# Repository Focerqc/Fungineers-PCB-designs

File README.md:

# Fungineers PCB designs

Boards for Fungineers hardware: the 32s pack BMS, the Superflux hall board, Funwheel light bars, and the connectors that sit in the controller box.

A reference photo, an OEM drawing, or a chip vendor's eval board tells us the job and the shape. The board in this repo is finished when it does that job with the parts that are already on it. A different FET, a module instead of a bare chip, or a bleed resistor the eval board never had is fine when the circuit still measures, drives, or lights what it has to. A silk screen that matches a photo, with nets that do not complete the job, is not finished.

## Boards

| Folder | Status | Job |
|---|---|---|
| [`qfbms32 ai pcb/`](qfbms32%20ai%20pcb/README.md) | Incomplete | 32s BMS. Dual BQ76952, ESP32-C3, pack and charge connectors, cell taps, thermistors, CAN. Parts are placed. The circuit is not finished. |
| [`sf hall ai pcb/`](sf%20hall%20ai%20pcb/README.md) | Laid out | Hall board for the Superflux stator. Three sensors on the stator pitch, purple mask, ENIG. |
| [`Funwheel LED strips/`](Funwheel%20LED%20strips/README.md) | Laid out | Funwheel X7 headlight, taillight, and Thor300 status bars. Each size has its own readme. |
| [`footpad connector controller box side/`](footpad%20connector%20controller%20box%20side/README.md) | Laid out | Small breakouts for the controller enclosure: 5-pin Amphenol and 6-pin Switchcraft / Molex. |
| [`GTFO/`](GTFO/README.md) | Photos only | Reference photos for the GTFO lights and the GTS-FO BMS adapter. The laid-out LED boards are under `Funwheel LED strips/`. |
| [`FM VFBMS adapter/`](FM%20VFBMS%20adapter/README.md) | Stopped | Adapter between a Fungineers BMS and the GTFO controller. No board was made. |
| `_reference/firmware/` | Notes | Notes for the smaller charge-only VBMS32, not the 32s board. |
| `_tools/` | Local tools | Board boxes on port 5180. BMS progress, read from the PCB file, on port 5181. |

## KiCad

Boards are KiCad 10 projects. Open the `.kicad_pro` in the folder you mean to work on. Scripts that import `pcbnew` have to run with `C:\Program Files\KiCad\10.0\bin\python.exe`.

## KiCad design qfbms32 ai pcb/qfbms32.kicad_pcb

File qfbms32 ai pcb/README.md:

# qfbms32

32-series BMS for a Fungineers pack. The board is a long strip, about 130 × 32 mm, two layers.

The parts are already placed to match the photos in `_reference/user_photos/`. Those positions, rotations, and packages stay. The work left is electrical: the placed parts have to do the BMS job.

## The job

The pack harness is `_reference/vfbms32_wiring_32s_best.jpg`. That drawing says which wire lands where. It is not a schematic.

| What the pack needs | On this board |
|---|---|
| Pack positive and negative | `J_BAT1` — TOP CELL is `CELL32`, BOT is `CELL0` |
| Charger | `J_CHG1` — `CHG+` / `CHG−` |
| 32 series cells, 33 taps | `J_CELL4` … `J_CELL1`, left to right `CELL32` … `CELL0` |
| Four thermistors | `J_T1` … `J_T4` |
| ESC CAN and 5 V | `J_COMM1`, through the isolator `U7` |
| Enable, buzzer, USB | Have to exist as a circuit, not only as a picture on the harness sheet |

Behind those connectors the board has to:

- Measure every cell on two BQ7695202s. `U_BQ1` is the low 16 (`CELL0`…`CELL16`). `U_BQ2` is the high 16 (`CELL16`…`CELL32`).
- Measure pack current on the shunt (`R_SH1`, `R_SH2`) through `SRP` / `SRN`.
- Bias and read the thermistors.
- Let the ESP32-C3 (`U_ESP1`) talk to both monitors.
- Switch charge (`Q1`) and discharge (`Q2`). `U_SSR1` is the gate helper that is actually placed. The BQ charge and discharge pins can drive gates too, once they are wired.
- Power the logic. `U4` is the buck that is placed for that.

The TI BQ76952 datasheet and EVM (under `_reference/ti_bq76952/`) supply pin function and the usual values: 20 Ω and 0.22 µF on each cell input, regulator caps, a sense filter, 10 kΩ thermistor bias. Use those values on the parts that are already here. Do not move a part to make the eval-board layout fit.

The placed chip stays even when it is a different part than the reference. `U_ESP1` is an ESP32-C3-MINI-1. The FETs are AGM15T03LL. The relay is an H2440. `R_B1`–`R_B33` are the 27 Ω bleed row beside the cell connectors. If a placed part has no pin for a function the reference wanted, stop and say which ref and which pin.

## Where it stands

This folder is the only copy of the board. Scored from the PCB file, not from notes. Open the progress dashboard and hit Reload after the board changes:

```powershell
python _tools/progress_dashboard/server.py
# http://localhost:5181
```

As of 27 Oct 2026 the file says:

- Connector names for pack, charge, the 33 cell taps, the four temps, and CAN match the harness.
- All 32 cell taps share copper with their filter resistor (`R_F`, 20 Ω). None of those resistors reach a BQ pin. The 0.22 µF caps (`C_F`) are on the back with nets and no copper.
- `U_BQ1` has 24 of 48 pins named. `U_BQ2` has 22. No BQ pin has copper to another part. Regulator, I2C, and the BQ FET-driver pins are empty. `BAT` is shorted to the `VC16` net. `VC0` on `U_BQ1` is tied straight to `CELL0`.
- The fuse input shares copper with TOP CELL. The fuse does not reach the FET drains. The shunt does not reach `SRP` / `SRN`. Neither FET gate reaches a driver.
- `U_ESP1`, USB-C, and the buck have no nets. There is no enable switch. The buzzer has a net name and nothing driving it.
- `R_B1`–`R_B33` are placed and unnetted. Leave them where they are.

The PCB pad nets are the working copy. The schematic has labels for the same idea and is not ahead of the board.

## Files

| Path | What it is |
|---|---|
| `qfbms32.kicad_pro` | KiCad 10 project |
| `qfbms32.kicad_pcb` | Layout. This is the board. |
| `qfbms32.kicad_sch` | Schematic |
| `WORKING_TOPOLOGY.md` | Net names for the harness and the two monitors |
| `qfbms.pretty/` | Footprints that are not in KiCad stock |
| `_reference/vfbms32_wiring_32s_best.jpg` | Pack harness drawing |
| `_reference/user_photos/` | The placed board, which the footprints have to match |
| `_reference/ti_bq76952/` | Datasheet, EVM guide, TIDA-010208 |
| `.history/` | Copies taken before large edits |
| `scratch/` | One-off scripts and the AGM pinout notes. Not part of the design. |

## Editing

Do not move, rotate, or swap a footprint to copy TI, to open a routing channel, or because the part looks unused. Route around it. Ask before a position, a footprint, or a value changes. The same rule is in `.cursor/rules/qfbms32-placement.mdc`.

KiCad's Python, for anything that imports `pcbnew`:

```powershell
& "C:\Program Files\KiCad\10.0\bin\python.exe" script.py
```

The other local tool, board boxes, is the placement viewer on port 5180 (`python _tools/pcb_dashboard/server.py`). It does not score whether the circuit works.

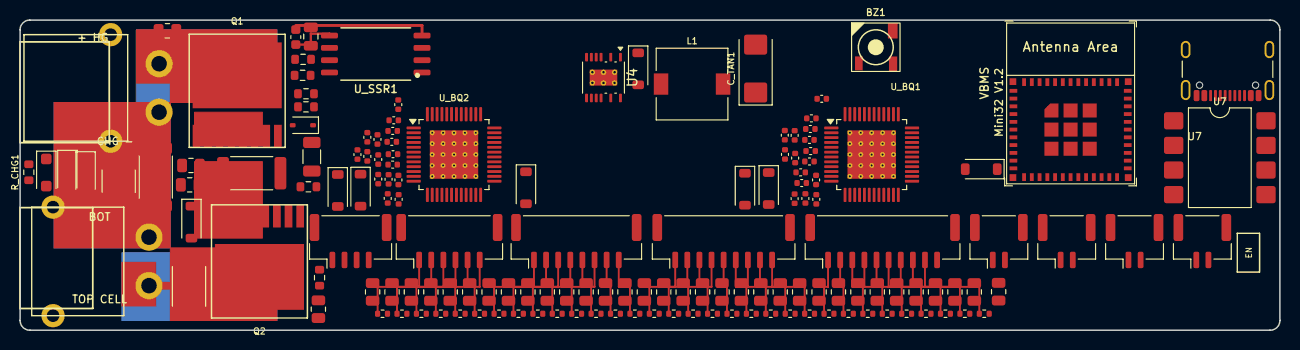
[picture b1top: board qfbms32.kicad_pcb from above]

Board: 2 copper layers, 130.0 x 32.0 mm, 150 parts (0 on the bottom side), 85 nets.

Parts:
BZ1: FUET-5030; Buzzer_5.0x5.0mm_SMD
C_DISC: 10uF; C_1206_3216Metric
C_F1, C_F2, C_F3, C_F4, C_F5, C_F6, C_F7, C_F8, C_F9, C_F10, C_F11, C_F12, C_F13, C_F14, C_F15, C_F16, C_F17, C_F18, C_F19, C_F20, C_F21, C_F22, C_F23, C_F24, C_F25, C_F26, C_F27, C_F28, C_F29, C_F30, C_F31, C_F32: 0.22uF; C_0402_1005Metric
C_FLT1: 10uF_100V; C_1812_4532Metric
C_SSR1: 100nF; C_0603_1608Metric
C_SSR2: 1uF; C_0805_2012Metric
C_TAN1: 100uF_16V; CP_EIA-6032-28_Kemet-C
D_BST1: Schottky; D_SOD-123
D_CHG1, D_CHG2, D_CHG3: DSK320; D_SOD-123F
D_GS1: PDZ16B; D_SOD-323
D_PRI1, D_PRI2, D_PRI3: D_Schottky; D_SOD-123
D_S1: TVS; D_SOD-123
D_SEC1, D_SEC2, D_SEC3: D_Schottky; D_SOD-123
F1: JT 15A; Fuse_2512_6332Metric
FB1: Unmarked; R_0603_1608Metric
J_BAT1: XT30PW-M (BAT); XT30PW-M_Lugs
J_CELL1: 0-8; JST_GH_BM10B-GHS-TBT_1x10-1MP_P1.25mm_Vertical
J_CELL2: 9-16; JST_GH_BM09B-GHS-TBT_1x09-1MP_P1.25mm_Vertical
J_CELL3: 17-24; JST_GH_BM08B-GHS-TBT_1x08-1MP_P1.25mm_Vertical
J_CELL4: 25-32; JST_GH_BM06B-GHS-TBT_1x06-1MP_P1.25mm_Vertical
J_CHG1: XT30PW-F (CHG); XT30PW-F_Lugs
J_COMM1: CAN/5V; JST_GH_BM04B-GHS-TBT_1x04-1MP_P1.25mm_Vertical
J_T1: T1; JST_GH_BM02B-GHS-TBT_1x02-1MP_P1.25mm_Vertical
J_T2: T2; JST_GH_BM02B-GHS-TBT_1x02-1MP_P1.25mm_Vertical
J_T3: T3; JST_GH_BM02B-GHS-TBT_1x02-1MP_P1.25mm_Vertical
J_T4: T4; JST_GH_BM02B-GHS-TBT_1x02-1MP_P1.25mm_Vertical
J_USB1: USB-C; USB_C_Receptacle_16P
L1: 180uH_181; L_7.3x7.3_H4.5
Q1, Q2: AGM15T03LL; TOLL-8_AGM15T03LL
R_B1, R_B2, R_B3, R_B4, R_B5, R_B6, R_B7, R_B8, R_B9, R_B10, R_B11, R_B12, R_B13, R_B14, R_B15, R_B16, R_B17, R_B18, R_B19, R_B20, R_B21, R_B22, R_B23, R_B24, R_B25, R_B26, R_B27, R_B28, R_B29, R_B30, R_B31, R_B32, R_B33: 27R0; R_0805_2012Metric
R_CHG1: 100k; R_0603_1608Metric
R_CHG2: 2203; R_0805_2012Metric
R_DSG1: 1000; R_0805_2012Metric
R_F1, R_F2, R_F3, R_F4, R_F5, R_F6, R_F7, R_F8, R_F9, R_F10, R_F11, R_F12, R_F13, R_F14, R_F15, R_F16, R_F17, R_F18, R_F19, R_F20, R_F21, R_F22, R_F23, R_F24, R_F25, R_F26, R_F27, R_F28, R_F29, R_F30, R_F31, R_F32: 20R; R_0402_1005Metric
R_G1: 01X; R_0603_1608Metric
R_GS1: 474; R_0603_1608Metric
R_S1, R_S2: 1000; R_0805_2012Metric
R_SEC1: 01X; R_0603_1608Metric
R_SH1, R_SH2: R001; R_2512_6332Metric
R_SSR1: 01X; R_0603_1608Metric
R_SSR2: 10k; R_0603_1608Metric
U4: LTC7138; Analog_MSOP-12-16-1EP_3x4.039mm_P0.5mm_EP1.651x2.845mm_Ther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
U7: ISO1050 (DUB-8); SMDIP-8_W9.53mm
U_BQ1: BQ7695202 (IC1); TQFP-48-1EP_7x7mm_P0.5mm_EP5x5mm_ThermalVias
U_BQ2: BQ7695202 (IC2); TQFP-48-1EP_7x7mm_P0.5mm_EP5x5mm_ThermalVias
U_ESP1: ESP32-C3-MINI-1
U_SSR1: GSRELAY; H2440_SSR

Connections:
5VExt: J_COMM1.4, U7.8
+3V3: BZ1.1, U7.1
BQ1_VC1: C_F1.1, C_F2.2, R_F32.2, U_BQ1.15
BQ1_VC2: C_F2.1, C_F3.2, R_F31.2, U_BQ1.14
BQ1_VC3: C_F3.1, C_F4.2, R_F30.2, U_BQ1.13
BQ1_VC4: C_F4.1, C_F5.2, R_F29.2, U_BQ1.12
BQ1_VC5: C_F5.1, C_F6.2, R_F28.2, U_BQ1.11
BQ1_VC6: C_F6.1, C_F7.2, R_F27.2, U_BQ1.10
BQ1_VC7: C_F7.1, C_F8.2, R_F26.2, U_BQ1.9
BQ1_VC8: C_F8.1, C_F9.2, R_F25.2, U_BQ1.8
BQ1_VC9: C_F9.1, C_F10.2, R_F24.2, U_BQ1.7
BQ1_VC10: C_F10.1, C_F11.2, R_F23.2, U_BQ1.6
BQ1_VC11: C_F11.1, C_F12.2, R_F22.2, U_BQ1.5
BQ1_VC12: C_F12.1, C_F13.2, R_F21.2, U_BQ1.4
BQ1_VC13: C_F13.1, C_F14.2, R_F20.2, U_BQ1.3
BQ1_VC14: C_F14.1, C_F15.2, R_F19.2, U_BQ1.2
BQ1_VC15: C_F15.1, C_F16.2, R_F18.2, U_BQ1.1
BQ1_VC16: C_F16.1, R_F17.2, U_BQ1.48
BQ2_VC1: C_F17.1, C_F18.2, R_F16.2, U_BQ2.15
BQ2_VC2: C_F18.1, C_F19.2, R_F15.2, U_BQ2.14
BQ2_VC3: C_F19.1, C_F20.2, R_F14.2, U_BQ2.13
BQ2_VC4: C_F20.1, C_F21.2, R_F13.2, U_BQ2.12
BQ2_VC5: C_F21.1, C_F22.2, R_F12.2, U_BQ2.11
BQ2_VC6: C_F22.1, C_F23.2, R_F11.2, U_BQ2.10
BQ2_VC7: C_F23.1, C_F24.2, R_F10.2, U_BQ2.9
BQ2_VC8: C_F24.1, C_F25.2, R_F9.2, U_BQ2.8
BQ2_VC9: C_F25.1, C_F26.2, R_F8.2, U_BQ2.7
BQ2_VC10: C_F26.1, C_F27.2, R_F7.2, U_BQ2.6
BQ2_VC11: C_F27.1, C_F28.2, R_F6.2, U_BQ2.5
BQ2_VC12: C_F28.1, C_F29.2, R_F5.2, U_BQ2.4
BQ2_VC13: C_F29.1, C_F30.2, R_F4.2, U_BQ2.3
BQ2_VC14: C_F30.1, C_F31.2, R_F3.2, U_BQ2.2
BQ2_VC15: C_F31.1, C_F32.2, R_F2.2, U_BQ2.1
BQ2_VC16: C_F32.1, R_F1.2, U_BQ2.48
CANH: J_COMM1.1, U7.7
CANL: J_COMM1.2, U7.6
CELL0: C_F1.2, J_BAT1.2, J_CELL1.10, R_SH1.1, U_BQ1.16
CELL1: J_CELL1.9, R_F32.1
CELL2: J_CELL1.8, R_F31.1
CELL3: J_CELL1.7, R_F30.1
CELL4: J_CELL1.6, R_F29.1
CELL5: J_CELL1.5, R_F28.1
CELL6: J_CELL1.4, R_F27.1
CELL7: J_CELL1.3, R_F26.1
CELL8: J_CELL1.2, R_F25.1
CELL9: J_CELL1.1, R_F24.1
CELL10: J_CELL2.9, R_F23.1
CELL11: J_CELL2.8, R_F22.1
CELL12: J_CELL2.7, R_F21.1
CELL13: J_CELL2.6, R_F20.1
CELL14: J_CELL2.5, R_F19.1
CELL15: J_CELL2.4, R_F18.1
CELL16: C_F17.2, J_CELL2.3, R_F17.1, U_BQ2.16
CELL17: J_CELL2.2, R_F16.1
CELL18: J_CELL2.1, R_F15.1
CELL19: J_CELL3.8, R_F14.1
CELL20: J_CELL3.7, R_F13.1
CELL21: J_CELL3.6, R_F12.1
CELL22: J_CELL3.5, R_F11.1
CELL23: J_CELL3.4, R_F10.1
CELL24: J_CELL3.3, R_F9.1
CELL25: J_CELL3.2, R_F8.1
CELL26: J_CELL3.1, R_F7.1
CELL27: J_CELL4.6, R_F6.1
CELL28: J_CELL4.5, R_F5.1
CELL29: J_CELL4.4, R_F4.1
CELL30: J_CELL4.3, R_F3.1
CELL31: J_CELL4.2, R_F2.1
CELL32: F1.1, J_BAT1.1, J_CELL4.1, R_F1.1, U_SSR1.6
CELL32_FUSED: F1.2, Q1.D, Q2.D
CHG+: D_GS1.2, J_CHG1.1, Q1.2, Q1.3, Q1.4, Q1.5, Q1.6, Q1.7, Q1.8, R_GS1.2
CHG-: J_CHG1.2, R_SH2.2
GND: C_SSR1.2, C_SSR2.2, J_T1.2, J_T2.2, J_T3.2, J_T4.2, R_SSR2.2, U7.4, U_BQ1.17, U_BQ2.17, U_SSR1.4
ISO_GND: J_COMM1.3, U7.5
PACK+: Q2.2, Q2.3, Q2.4, Q2.5, Q2.6, Q2.7, Q2.8
Q1_GATE: D_GS1.1, Q1.1, R_G1.1, R_GS1.1, R_SSR1.2, R_SSR2.1
SHUNT_MID: R_SH1.2, R_SH2.1
SRN: U_BQ1.20, U_BQ2.20
SRP: U_BQ1.18, U_BQ2.18
SSR_OUT_CHG: R_G1.2, R_SSR1.1
TS1: J_T1.1, U_BQ1.21
TS2: J_T2.1, U_BQ1.22
TS3: J_T3.1, U_BQ1.23
TS4: J_T4.1, U_BQ2.21
VBOOST: C_SSR1.1, C_SSR2.1, U_SSR1.5

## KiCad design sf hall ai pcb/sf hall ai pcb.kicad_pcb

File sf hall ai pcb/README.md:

# Superflux Hall Sensor PCB

**Status:** Laid out. Three sensors sit on the stator pitch. The STEP export still does not model plated walls inside the hall slots.

High-precision hall sensor PCB designed for the Fungineers Superflux motor.

---

## 1. Design Overview

- **Layer Stackup**: 2-Layer FR4, 1.6 mm thickness
- **Solder Mask**: Purple (`#43135C` / `#591271`), matching Superflux motor branding
- **Surface Finish**: ENIG (Electroless Nickel Immersion Gold)
- **Stator Alignment**: Derived from original stator drawing `sf hall locations.DXF` (27-slot stator, $13.\overline{3}^\circ$ pitch)

### Hall Sensor Centers (at $R = 56.15\,\text{mm}$):
- **U1**: $23^\circ 20'$ ($23.3333^\circ$)
- **U2**: $63^\circ 20'$ ($63.3333^\circ$)
- **U3**: $103^\circ 20'$ ($103.3333^\circ$)
- **Sensor Pitch**: Exactly $40.000^\circ$ (3 stator teeth) between sensors.
- **Pin Spread**: $\pm 2.45^\circ$ ($2.40\,\text{mm}$ pitch) between outer pins and centered middle pin.

---

## 2. TODO / Future Work: Hall Slot 3D Edge Plating

> [!WARNING]
> **CAD Modeling Note — Hall Slot Edge Plating**
>
> The hall sensor slots currently have:
> - $1.25\,\text{mm}$ wide clean U-slots on `Edge.Cuts` with semicircular rounded bottoms ($R = 0.625\,\text{mm}$).
> - U-shaped copper solder lands on `F.Cu` and `B.Cu` framing each slot with zero protrusion into the slot or past the outer board edge.
>
> **Known CAD Limitation**:
> In physical manufacturing (e.g., JLCPCB castellated holes / edge plating), the internal vertical walls of these slots are plated with copper and immersion gold. However, the standard KiCad STEP export pipeline (`kicad-cli pcb export step`) does not generate 3D vertical copper plating along internal `Edge.Cuts` slot profiles—it only exports planar surface copper pads and cylindrical through-hole barrels.
>
> **Action Required**:
> The pads are close and functional for component clearance and leg passage, but need work later to accurately model the vertical edge plating in the CAD/STEP assembly (either via custom 3D STEP body injection or an updated KiCad castellated modeling workflow).

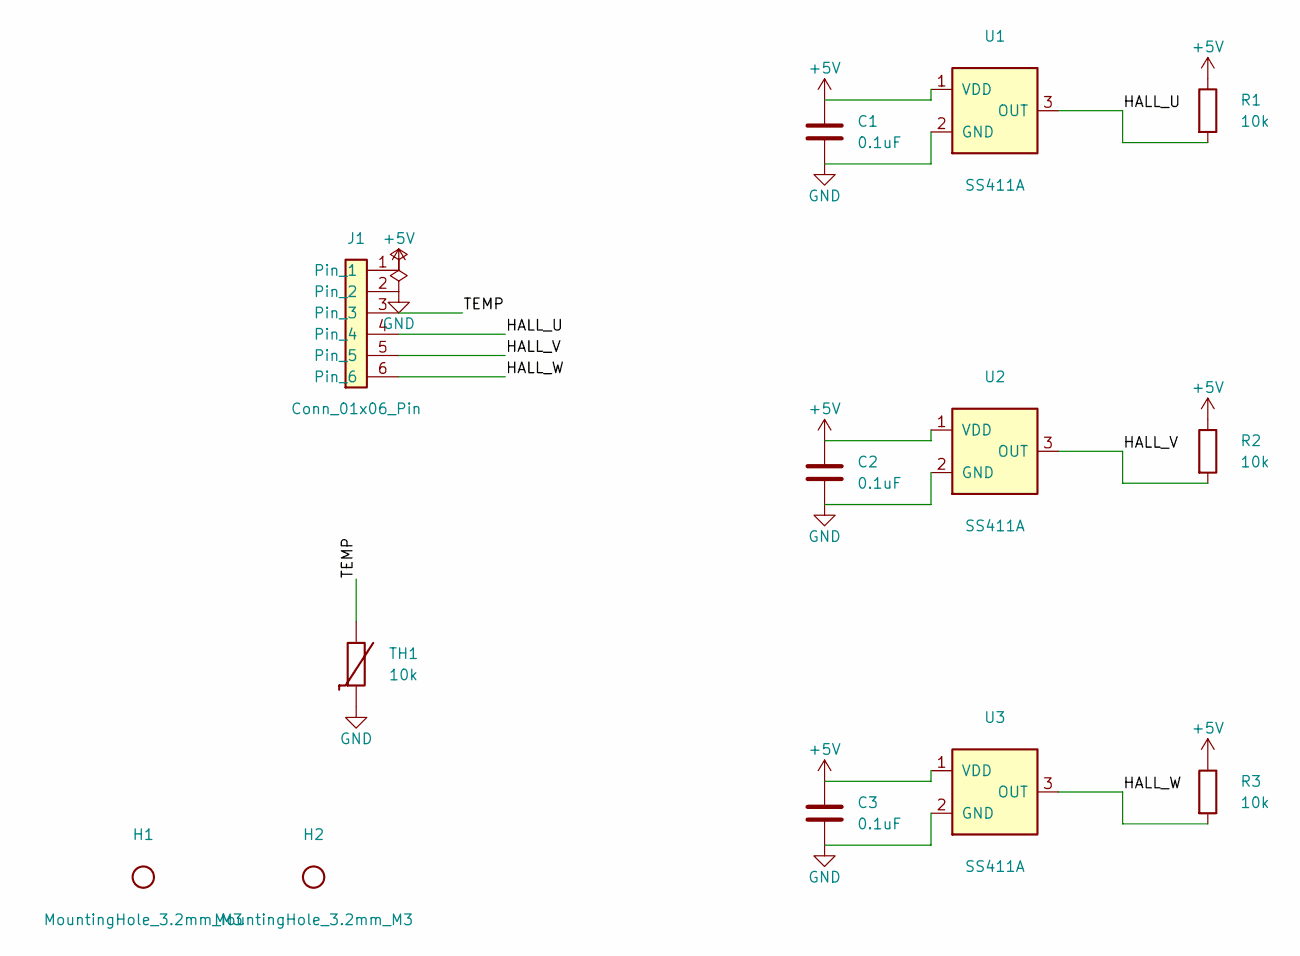
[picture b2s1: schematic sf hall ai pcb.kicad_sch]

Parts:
C1, C2, C3: 0.1uF; C_0805_2012Metric; MPN CL21B104KBCNNNC
H1, H2: MountingHole_3.2mm_M3
J1: Conn_01x06_Pin; PinHeader_1x06_P2.54mm_Vertical; MPN 68000-106HLF
R1, R2, R3: 10k; R_0805_2012Metric; MPN RC0805JR-0710KL
TH1: 10k; R_0805_2012Metric; MPN NTHS0805N02N1002JE
U1, U2, U3: SS411A; TO-92_Inline_Wide; MPN SS411A

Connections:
+5V: C1.1, C2.1, C3.1, J1.1, R1.1, R2.1, R3.1, U1.1 (VDD), U2.1 (VDD), U3.1 (VDD)
GND: C1.2, C2.2, C3.2, J1.2, TH1.2, U1.2 (GND), U2.2 (GND), U3.2 (GND)
HALL_U: J1.4, R1.2, U1.3 (OUT)
HALL_V: J1.5, R2.2, U2.3 (OUT)
HALL_W: J1.6, R3.2, U3.3 (OUT)
TEMP: J1.3, TH1.1

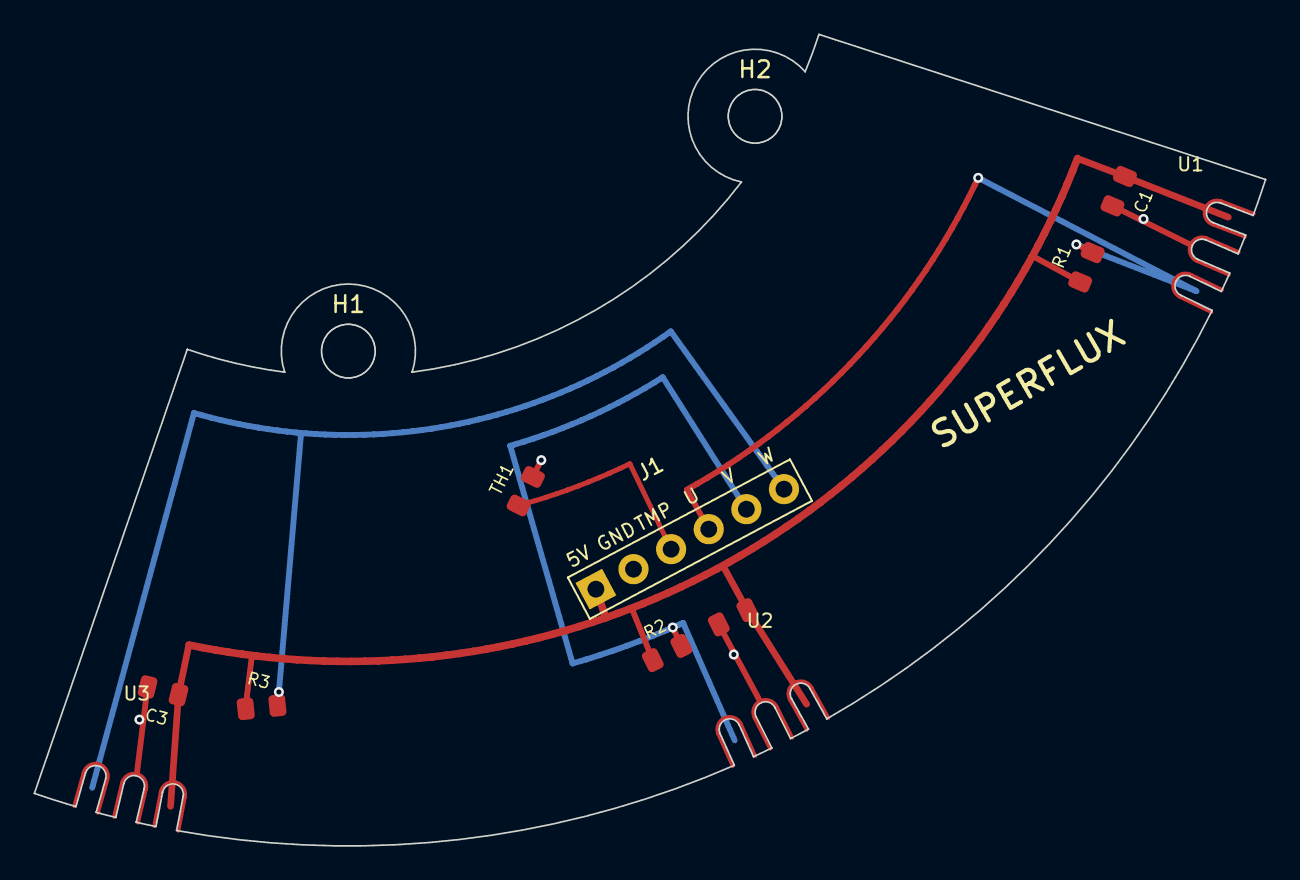
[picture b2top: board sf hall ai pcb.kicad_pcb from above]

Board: 2 copper layers, 73.4 x 48.4 mm, 13 parts (0 on the bottom side), 6 nets.

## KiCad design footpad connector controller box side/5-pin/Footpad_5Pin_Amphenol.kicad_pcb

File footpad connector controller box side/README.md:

# Controller-Box-Side PEV Breakout & Adapter PCBs

**Status:** Laid out. The 5-pin Amphenol, 6-pin Switchcraft, and Molex header boards are in this folder.

High-reliability, vibration-resistant breakout and adapter PCBs designed to mount directly inside the controller enclosure of PEV (Personal Electric Vehicle / VESC) builds such as Onewheel XR, Plus, Pint, Pint X, and GT platforms.

---

## 1. Directory Structure

```text
footpad connector controller box side/
├── 5-pin/
│   ├── Footpad_5Pin_Amphenol.kicad_pro       # GT / Pint 5-Pin Project (Amphenol AU-05)
│   ├── Footpad_5Pin_Amphenol.kicad_sch       # Schematic (3.3V excited, ADC1, ADC2)
│   ├── Footpad_5Pin_Amphenol.kicad_pcb       # 16x16mm PCB (0 DRC violations)
│   └── fp-lib-table                          # Project Footprint Library Table
├── 6-pin/
│   ├── Footpad_6Pin_Switchcraft/             # Universal 6-Pin Project (Switchcraft EN3)
│   │   ├── Footpad_6Pin_Switchcraft.kicad_pro
│   │   ├── Footpad_6Pin_Switchcraft.kicad_sch # Dual-Use: Motor Hall & Footpad
│   │   ├── Footpad_6Pin_Switchcraft.kicad_pcb # 20x20mm PCB (JST-GH + Solder Pads, 0 DRC violations)
│   │   └── fp-lib-table
│   └── Molex_MX150L_6Pin_Header/             # 6-Circuit Vertical Header Faceplate
│       ├── Molex_MX150L_6Pin_Header.kicad_pro
│       ├── Molex_MX150L_6Pin_Header.kicad_sch
│       ├── Molex_MX150L_6Pin_Header.kicad_pcb
│       └── fp-lib-table
├── references/                               # Archived Reference Documents & Diagrams
│   ├── GT_Pint_5Pin_Handwritten_Reference.jpg
│   ├── XR_6Pin_Footpad_Handwritten_Reference.jpg
│   ├── XR_Hypercore_Motor_Hall_Switchcraft_6Pin_Reference.png
│   ├── Pint_GT_5Pin_Wiring_Schematic_Reference.png
│   └── KiCad_PCB_Screenshot_Reference.png
├── footpad_shared.pretty/                    # Shared KiCad Footprint Library
└── README.md
```

---

## 2. Hardware Specifications & Connectors

| Connector Type | Manufacturer & Part Number | Application | Board Dimensions | Primary Termination | Backup Termination |
| :--- | :--- | :--- | :--- | :--- | :--- |
| **5-Pin Circular** | Amphenol LTW `AU-05PMMS-LC7001` | GT / Pint Footpad | $16 \times 16\text{ mm}$ (chamfered) | JST-PH 3-Pin (2.00mm pitch) | 3 Plated Oval Wire Solder Pads |
| **6-Pin Circular** | Switchcraft `EN3P6MX` | **Universal**: XR Motor Hall / Footpad | $20 \times 20\text{ mm}$ (chamfered) | **SMD JST-GH 6-Pin (1.25mm pitch)** | **6 Plated Through-Hole Solder Pads (2.0mm pitch)** |
| **Modular Header** | Molex MX150L `19428-0012` | Controller Faceplate Breakout | $88 \times 28\text{ mm}$ (flanged) | Dual-row solder bars & harness | Solder pads |

---

## 3. Pinouts & Electrical Mappings

### A. GT / Pint 5-Pin Connector (Amphenol AU-05)
*Connector Geometry: 4 Outer Pins in Square ($r = 2.0\text{ mm}$) + Pin 5 at Center `(0, 0)`. Notch at 12 o'clock.*

| Pin # | Solder Side Position (Notch at Top) | VESC Signal | Hybrid Pad Destination | Function / Notes |
| :---: | :--- | :---: | :---: | :--- |
| **1** | Top-Right (`X = +1.414, Y = -1.414`) | **`3.3V`** | Pad 3 (`3.3V`) | FSR Common Excitation Rail |
| **2** | Bottom-Right (`X = +1.414, Y = +1.414`)| `NC` | — | Unconnected / Spare |
| **3** | Bottom-Left (`X = -1.414, Y = +1.414`) | **`ADC1`** | Pad 2 (`ADC1`) | Sensor Half 1 (VESC ADC1 Input) |
| **4** | Top-Left (`X = -1.414, Y = -1.414`) | **`ADC2`** | Pad 1 (`ADC2`) | Sensor Half 2 (VESC ADC2 Input) |
| **5** | Center (`X = 0, Y = 0`) | `NC` | — | Ground / Shield / Spare |

> **Note on Excitation Voltage**: VESC ADC inputs utilize internal/external pull-down resistors to Ground. The common footpad excitation must connect to **`3.3V`** so that depressing the FSR creates a positive voltage divider signal into `ADC1` and `ADC2`.

---

### B. Universal 6-Pin Switchcraft EN3 Connector (Motor Hall / Footpad)
*Connector Geometry: 5 Outer Pins ($r = 2.4\text{ mm}$, $72^\circ$ spacing) + Pin 6 at Center `(0, 0)`. Notch at 12 o'clock.*

| Pin # | Solder Side Position (Notch at Top) | Motor Hall Signal | Footpad Signal | Motor Wire Color | JST-GH Pin | Backup Solder Pad |
| :---: | :--- | :--- | :--- | :---: | :---: | :---: |
| **1** | Top-Right (`X = +1.41, Y = -1.94`) | **`HALL 1`** (`H1`) | **`ADC 1`** | **Green** | Pin 1 | Pad 1 (Right) |
| **2** | Bottom-Right (`X = +2.28, Y = +0.74`) | **`HALL 2`** (`H2`) | **`ADC 2`** | **Blue** | Pin 2 | Pad 2 |
| **3** | Bottom (`X = 0.0, Y = +2.40`) | **`GND`** | **`GND`** (Shield) | **Black** | Pin 3 | Pad 3 |
| **4** | Bottom-Left (`X = -2.28, Y = +0.74`) | **`5V`** (Hall Power) | `NC` | **Red** | Pin 4 | Pad 4 |
| **5** | Top-Left (`X = -1.41, Y = -1.94`) | **`TEMP`** (Motor NTC)| `NC` | **White** | Pin 5 | Pad 5 |
| **6** | Center (`X = 0.0, Y = 0.0`) | **`HALL 3`** (`H3`) | **`3.3V`** (Excitation) | **Yellow** | Pin 6 | Pad 6 (Left) |

### Dual Silkscreen Markings on Universal 6-Pin PCB:
- **Front Silkscreen (`F.SilkS`)**:
  - Row 1 (Motor): `MOT:  H3   TMP   5V   GND   H2   H1`
  - Row 2 (Footpad): ` FP: 3.3V  NC    NC   GND  ADC2 ADC1`
- **Back Silkscreen (`B.SilkS`)**: Full quick-reference color-code reference chart:
  - `1: H1/ADC1 (GRN)`
  - `2: H2/ADC2 (BLU)`
  - `3: GND/GND (BLK)`
  - `4: 5V/NC   (RED)`
  - `5: TMP/NC  (WHT)`
  - `6: H3/3.3V (YEL)`

---

## 4. Fabrication & Verification

- **Layers**: 2-Layer (Top: `F.Cu`, Bottom: `B.Cu`)
- **Board Thickness**: 1.6 mm (FR-4)
- **Surface Finish**: Lead-Free HASL or ENIG
- **Copper Weight**: 1 oz (35 µm)
- **Minimum Trace / Space**: 0.35 mm / 0.35 mm (> 13.8 mil, exceeding standard fab limits)
- **KiCad DRC**: **0 DRC Violations, 0 Unconnected Items, 0 Footprint Errors** on both projects.

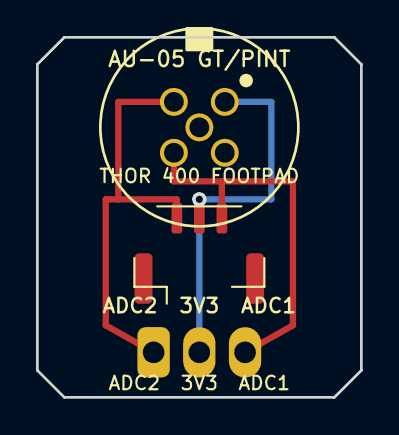
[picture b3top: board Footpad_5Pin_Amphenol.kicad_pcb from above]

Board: 2 copper layers, 18.0 x 20.0 mm, 3 parts (0 on the bottom side), 3 nets.

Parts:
J1: Amphenol_AU-05PMMS; Amphenol_AU-05PMMS-LC7001_Piggyback
J2: JST_GH_3P_Footpad; JST_GH_BM03B-GHS-TBT_1x03-1MP_P1.25mm_Vertical
J3: SolderPads_3Pin; SolderPads_3Pin_Universal

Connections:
3.3V: J1.1, J2.2, J3.2
ADC1: J1.3, J2.1, J3.3
ADC2: J1.4, J2.3, J3.1

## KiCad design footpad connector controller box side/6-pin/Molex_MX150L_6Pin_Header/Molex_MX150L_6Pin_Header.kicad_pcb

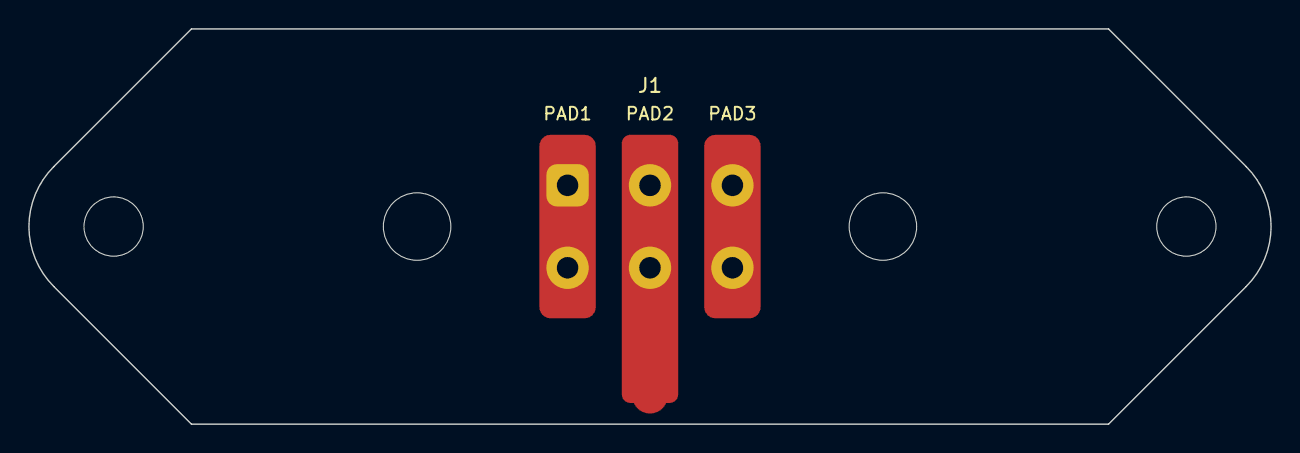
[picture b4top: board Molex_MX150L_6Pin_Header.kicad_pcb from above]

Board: 2 copper layers, 88.0 x 28.0 mm, 6 parts (0 on the bottom side), 3 nets.

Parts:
J1: 19428-0012; Molex_MX150L_19428-0012_2x03_P5.84mm_Vertical
MH1, MH2: MountingHole_4.2mm
PAD1: SolderPad_Left; SolderPad_VerticalBar_4x13mm
PAD2: SolderPad_Center; SolderPad_VerticalBar_4x19mm
PAD3: SolderPad_Right; SolderPad_VerticalBar_4x13mm

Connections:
NET_CENTER: J1.2, J1.5, PAD2.1
NET_LEFT: J1.1, J1.4, PAD1.1
NET_RIGHT: J1.3, J1.6, PAD3.1

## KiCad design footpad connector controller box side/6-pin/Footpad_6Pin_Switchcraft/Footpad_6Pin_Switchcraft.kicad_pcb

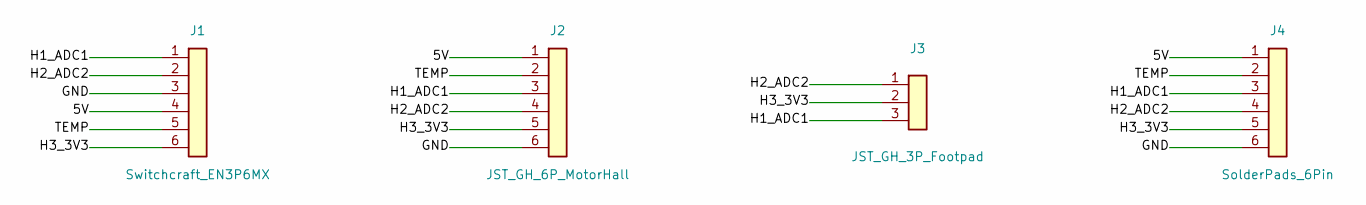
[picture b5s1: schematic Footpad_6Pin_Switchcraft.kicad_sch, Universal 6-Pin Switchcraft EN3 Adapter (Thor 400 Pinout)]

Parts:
J1: Switchcraft_EN3P6MX; Switchcraft_EN3P6MX_Piggyback
J2: JST_GH_6P_MotorHall; JST_GH_BM06B-GHS-TBT_1x06_P1.25mm_Vertical
J3: JST_GH_3P_Footpad; JST_GH_BM03B-GHS-TBT_1x03_P1.25mm_Vertical
J4: SolderPads_6Pin; SolderPads_6Pin_Universal

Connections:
5V: J1.4, J2.1, J4.1
GND: J1.3, J2.6, J4.6
H1_ADC1: J1.1, J2.3, J3.3, J4.3
H2_ADC2: J1.2, J2.4, J3.1, J4.4
H3_3V3: J1.6, J2.5, J3.2, J4.5
TEMP: J1.5, J2.2, J4.2

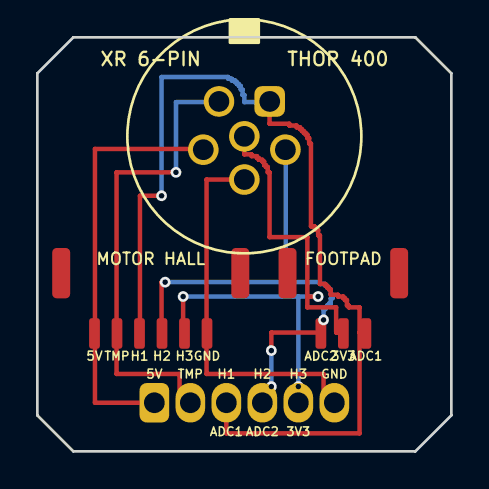
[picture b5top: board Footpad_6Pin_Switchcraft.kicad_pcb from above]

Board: 2 copper layers, 23.0 x 23.0 mm, 4 parts (0 on the bottom side), 6 nets.

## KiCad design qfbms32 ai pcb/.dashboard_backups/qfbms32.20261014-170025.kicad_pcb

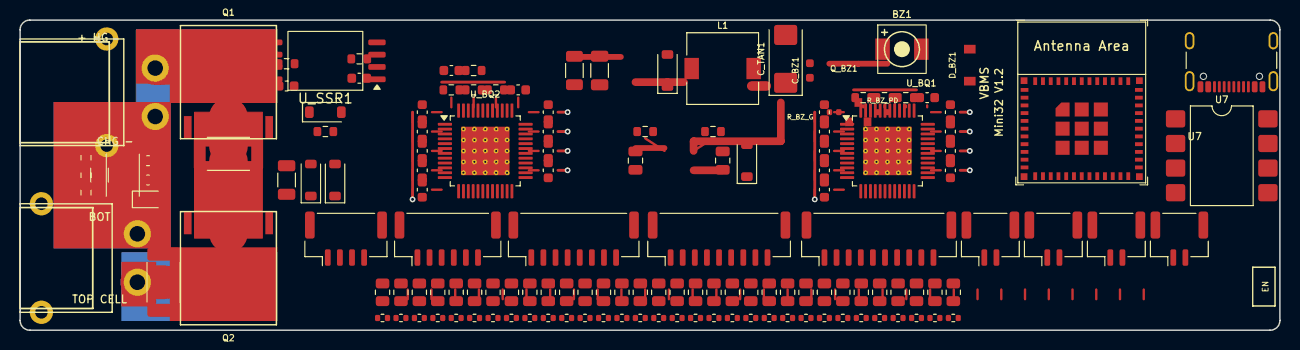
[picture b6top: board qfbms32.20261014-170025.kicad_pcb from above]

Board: 2 copper layers, 130.0 x 32.0 mm, 146 parts (0 on the bottom side), 4 nets.

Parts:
BZ1: MLT-5030; Buzzer_5.0x5.0mm_SMD
C_BQ1_BAT, C_BQ1_FLT1, C_BQ1_FLT2, C_BQ1_FLT3, C_BQ1_FLT4, C_BQ1_FLT5, C_BQ1_VDD, C_BQ2_BAT, C_BQ2_CP1, C_BQ2_FLT1, C_BQ2_FLT2, C_BQ2_FLT3, C_BQ2_FLT4, C_BQ2_FLT5, C_BQ2_VDD: 100nF; C_0603_1608Metric
C_BQ1_REG1, C_BQ1_REG2, C_BQ1_REG18, C_BQ2_REG1, C_BQ2_REG2, C_BQ2_REG18: 2.2uF; C_0603_1608Metric
C_BZ1: 1uF; C_0603_1608Metric
C_DISC: 10uF; C_1206_3216Metric
C_DRV1, C_DRV2: 100nF; C_0603_1608Metric
C_FLT1: 10uF_100V; C_1206_3216Metric
C_PWR1: 10uF; C_1206_3216Metric
C_PWR2, C_PWR3: 22uF; C_0805_2012Metric
C_S1, C_S2: 100nF; C_0603_1608Metric
C_TAN1: 100uF_16V; CP_EIA-6032-28_Kemet-C
D_BST1: Schottky; D_SOD-123
D_BZ1: B0540W; D_SOD-123
D_PWR1: Schottky; D_SOD-123
D_S1: TVS; D_SOD-323
D_SEC1, D_SEC2: D_Schottky; D_SOD-123
D_TVS1: TVS; D_SOD-123
D_V1, D_V2, D_V3: 0603; R_0603_1608Metric
F1: JT 18A; Fuse_2512_6332Metric
J_BAT1: XT30PW-M (BAT); XT30PW-M_Lugs
J_CELL1: 0-8; JST_GH_BM10B-GHS-TBT_1x10-1MP_P1.25mm_Vertical
J_CELL2: 9-16; JST_GH_BM09B-GHS-TBT_1x09-1MP_P1.25mm_Vertical
J_CELL3: 17-24; JST_GH_BM08B-GHS-TBT_1x08-1MP_P1.25mm_Vertical
J_CELL4: 25-32; JST_GH_BM06B-GHS-TBT_1x06-1MP_P1.25mm_Vertical
J_CHG1: XT30PW-F (CHG); XT30PW-F_Lugs
J_COMM1: CAN/5V; JST_GH_BM04B-GHS-TBT_1x04-1MP_P1.25mm_Vertical
J_T1: T1; JST_GH_BM02B-GHS-TBT_1x02-1MP_P1.25mm_Vertical
J_T2: T2; JST_GH_BM02B-GHS-TBT_1x02-1MP_P1.25mm_Vertical
J_T3: T3; JST_GH_BM02B-GHS-TBT_1x02-1MP_P1.25mm_Vertical
J_T4: T4; JST_GH_BM02B-GHS-TBT_1x02-1MP_P1.25mm_Vertical
J_USB1: USB-C; USB_C_Receptacle_16P
L1: 180uH_181; L_7.3x7.3_H4.5
Q1, Q2: AGM15T03LL; TOLL-8_AGM15T03LL
Q_BZ1: 2N7002; SOT-23
R_B1, R_B2, R_B3, R_B4, R_B5, R_B6, R_B7, R_B8, R_B9, R_B10, R_B11, R_B12, R_B13, R_B14, R_B15, R_B16, R_B17, R_B18, R_B19, R_B20, R_B21, R_B22, R_B23, R_B24, R_B25, R_B26, R_B27, R_B28, R_B29, R_B30, R_B31, R_B32: 27R0; R_0805_2012Metric
R_BK_FB1: 100k; R_0603_1608Metric
R_BK_FB2: 22k; R_0603_1608Metric
R_BQ1_PU1, R_BQ1_PU2, R_BQ2_PU1, R_BQ2_PU2: 4k7; R_0603_1608Metric
R_BQ1_PU3, R_BQ2_PU3, R_BQ2_PU4: 10k; R_0603_1608Metric
R_BZ_G: 100R; R_0402_1005Metric
R_BZ_PD: 10k; R_0402_1005Metric
R_DRV1, R_DRV2: 10k; R_0603_1608Metric
R_DRV3: 1k; R_0603_1608Metric
R_F1, R_F2, R_F3, R_F4, R_F5, R_F6, R_F7, R_F8, R_F9, R_F10, R_F11, R_F12, R_F13, R_F14, R_F15, R_F16, R_F17, R_F18, R_F19, R_F20, R_F21, R_F22, R_F23, R_F24, R_F25, R_F26, R_F27, R_F28, R_F29, R_F30, R_F31, R_F32: 100R; R_0402_1005Metric
R_PWR1: 10R0; R_1206_3216Metric
R_SH1, R_SH2: R001; R_2512_6332Metric
U7: ISO1050 (DUB-8); SMDIP-8_W9.53mm
U_BQ1: BQ7695202 (IC1); TQFP-48-1EP_7x7mm_P0.5mm_EP5x5mm_ThermalVias
U_BQ2: BQ7695202 (IC2); TQFP-48-1EP_7x7mm_P0.5mm_EP5x5mm_ThermalVias
U_ESP1: ESP32-C3-MINI-1
U_SSR1: GSRELAY; SOIC-8_7.5x5.85mm_P1.27mm

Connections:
+3V3: BZ1.1, C_BZ1.1, D_BZ1.1, U7.1
BUZZ_LOW: BZ1.2, D_BZ1.2
GND: C_BZ1.2, Q_BZ1.2, R_BZ_PD.2, U7.4
PIN_BUZZER: Q_BZ1.1, R_BZ_G.1, R_BZ_G.2, R_BZ_PD.1

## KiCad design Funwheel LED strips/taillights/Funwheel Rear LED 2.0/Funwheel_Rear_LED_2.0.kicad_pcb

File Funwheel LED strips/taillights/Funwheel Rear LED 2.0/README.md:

# Funwheel Rear LED 2.0 (Funwheel X7 Taillight)

**Status:** Laid out.

High-reliability 12V addressable RGB taillight LED PCB stick engineered for the **Funwheel X7** rear light cavity.

---

## 1. Physical & Mechanical Specifications

| Parameter | Value | Notes |
| :--- | :--- | :--- |
| **PCB Length** | **155.0 mm** | Matches Funwheel X7 rear chassis extrusion cavity |
| **PCB Width** | **6.85 mm** | Ultra-narrow strip profile |
| **PCB Thickness** | **1.5 mm** (or standard 1.6 mm) | Rigid 2-layer FR4 |
| **LED Package** | **5050 SMD 6-Pin (PLCC-6)** ($5.0 \times 5.0\text{ mm}$) | 6 solder points (3 on left side, 3 on right side) |
| **LED Count & Grouping** | **16 LEDs in 4 Groups of 4** | 4 optical segments ($8.0\text{ mm}$ intra-group pitch, $11.5\text{ mm}$ inter-group gap) |
| **Connector** | **JST GH 1.25mm 4-Pin SMT (Horizontal/Side-Entry)** | Part: `SM04B-GHS-TB`, rotated 90° along the board edge |
| **Passives Orientation** | **Vertical (Along Board Length)** | All 0603 caps & resistors turned 90° along length for optimal clearance |

---

## 2. Electrical Specifications & Pinout

### Operating Voltage & LEDs
* **LED Driver Type**: **SK6815 / WS2815 / GS8208 (6-Pin 5050)** (12V DC Addressable RGB LED with dual data / breakpoint resume).
* **Nominal Voltage**: **+12V DC** (from Funwheel X7 / VESC controller).
* **Color Sequence**: **GRB** 24-bit.
* **Signal Level**: 5V TTL logic.

### JST GH 4-Pin Silkscreen & Connector Mapping (SMT Backside, Rotated 90°)

Pins run along the board edge with silkscreen markings directly alongside the solder pads:

| Pin # | Silkscreen Marking | Signal Name | Function & Routing |
| :---: | :---: | :---: | :--- |
| **1** | **`in`** | **DATA_IN** | Data input from controller. Connects through $33\,\Omega$ resistor to `DIN`/`BIN` of LED #1. |
| **2** | **`out`** | **DATA_OUT** | Return data from LED #16 (`DOUT`). Connects through $33\,\Omega$ resistor to allow daisy-chaining directly to next strip via single harness! |
| **3** | **`g`** | **GND** | 0V Ground reference & power return plane. |
| **4** | **`12v`** | **+12V** | +12V DC power bus distributing power to all 16 LEDs. |

---

## 3. LED Array Coordinates (4 Groups of 4)

* **Group 1**:
  * D1: $Y = 6.5\text{ mm}$
  * D2: $Y = 14.5\text{ mm}$
  * D3: $Y = 22.5\text{ mm}$
  * D4: $Y = 30.5\text{ mm}$
* **Group 2** (after $6.5\text{ mm}$ optical gap):
  * D5: $Y = 42.0\text{ mm}$
  * D6: $Y = 50.0\text{ mm}$
  * D7: $Y = 58.0\text{ mm}$
  * D8: $Y = 66.0\text{ mm}$
* **Group 3** (after $6.5\text{ mm}$ optical gap):
  * D9: $Y = 77.5\text{ mm}$
  * D10: $Y = 85.5\text{ mm}$
  * D11: $Y = 93.5\text{ mm}$
  * D12: $Y = 101.5\text{ mm}$
* **Group 4** (after $6.5\text{ mm}$ optical gap):
  * D13: $Y = 113.0\text{ mm}$
  * D14: $Y = 121.0\text{ mm}$
  * D15: $Y = 129.0\text{ mm}$
  * D16: $Y = 137.0\text{ mm}$
* **Connector & Passives Zone**: $Y = 139.5\text{ mm}$ to $155.0\text{ mm}$.

---

## 4. Exported Models & Visualizations

* **STEP 3D Model**: [`Funwheel_Rear_LED_2.0.step`](Funwheel_Rear_LED_2.0.step)
* **3D Top View**: [`Funwheel_Rear_LED_2.0_3d_top.png`](Funwheel_Rear_LED_2.0_3d_top.png)
* **3D Bottom View**: [`Funwheel_Rear_LED_2.0_3d_bottom.png`](Funwheel_Rear_LED_2.0_3d_bottom.png)
* **2D Vector View**: [`Funwheel_Rear_LED_2.0_2d_view.png`](Funwheel_Rear_LED_2.0_2d_view.png)

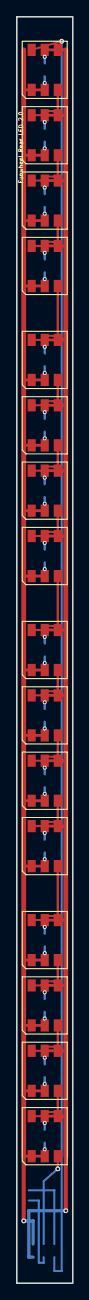
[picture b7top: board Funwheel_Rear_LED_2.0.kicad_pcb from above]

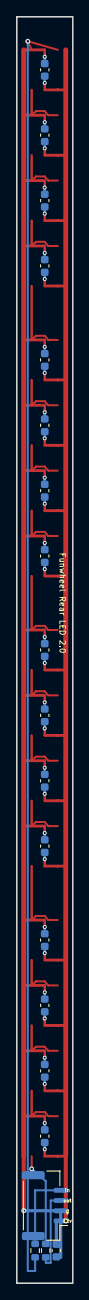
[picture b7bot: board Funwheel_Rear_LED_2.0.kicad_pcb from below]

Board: 2 copper layers, 6.8 x 155.0 mm, 36 parts (20 on the bottom side), 20 nets.

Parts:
C1, C2, C3, C4, C5, C6, C7, C8, C9, C10, C11, C12, C13, C14, C15, C16: 0.1uF; C_0603_1608Metric
C17: 10uF; C_0603_1608Metric
D1, D2, D3, D4, D5, D6, D7, D8, D9, D10, D11, D12, D13, D14, D15, D16: SK6815; LED_WS2812_PLCC6_5.0x5.0mm_P1.6mm
J1: BM04B-GHS-TBT; JST_GH_BM04B-GHS-TBT_1x04-1MP_P1.25mm_Vertical
R1, R2: 33R; R_0603_1608Metric

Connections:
+12V: C1.2, C2.2, C3.2, C4.2, C5.2, C6.2, C7.2, C8.2, C9.2, C10.2, C11.2, C12.2, C13.2, C14.2, C15.2, C16.2, C17.1, D1.1, D1.2, D2.1, D2.2, D3.1, D3.2, D4.1, D4.2, D5.1, D5.2, D6.1, D6.2, D7.1, D7.2, D8.1, D8.2, D9.1, D9.2, D10.1, D10.2, D11.1, D11.2, D12.1, D12.2, D13.1, D13.2, D14.1, D14.2, D15.1, D15.2, D16.1, D16.2, J1.1
DATA_IN: J1.4, R1.1
DATA_OUT: J1.3, R2.1
DIN_1: D1.4, D1.6, R1.2
DOUT_1: D1.3, D2.4, D2.6
DOUT_2: D2.3, D3.4, D3.6
DOUT_3: D3.3, D4.4, D4.6
DOUT_4: D4.3, D5.4, D5.6
DOUT_5: D5.3, D6.4, D6.6
DOUT_6: D6.3, D7.4, D7.6
DOUT_7: D7.3, D8.4, D8.6
DOUT_8: D8.3, D9.4, D9.6
DOUT_9: D9.3, D10.4, D10.6
DOUT_10: D10.3, D11.4, D11.6
DOUT_11: D11.3, D12.4, D12.6
DOUT_12: D12.3, D13.4, D13.6
DOUT_13: D13.3, D14.4, D14.6
DOUT_14: D14.3, D15.4, D15.6
DOUT_15: D15.3, D16.4, D16.6
GND: C1.1, C2.1, C3.1, C4.1, C5.1, C6.1, C7.1, C8.1, C9.1, C10.1, C11.1, C12.1, C13.1, C14.1, C15.1, C16.1, C17.2, D1.5, D2.5, D3.5, D4.5, D5.5, D6.5, D7.5, D8.5, D9.5, D10.5, D11.5, D12.5, D13.5, D14.5, D15.5, D16.5, J1.2
